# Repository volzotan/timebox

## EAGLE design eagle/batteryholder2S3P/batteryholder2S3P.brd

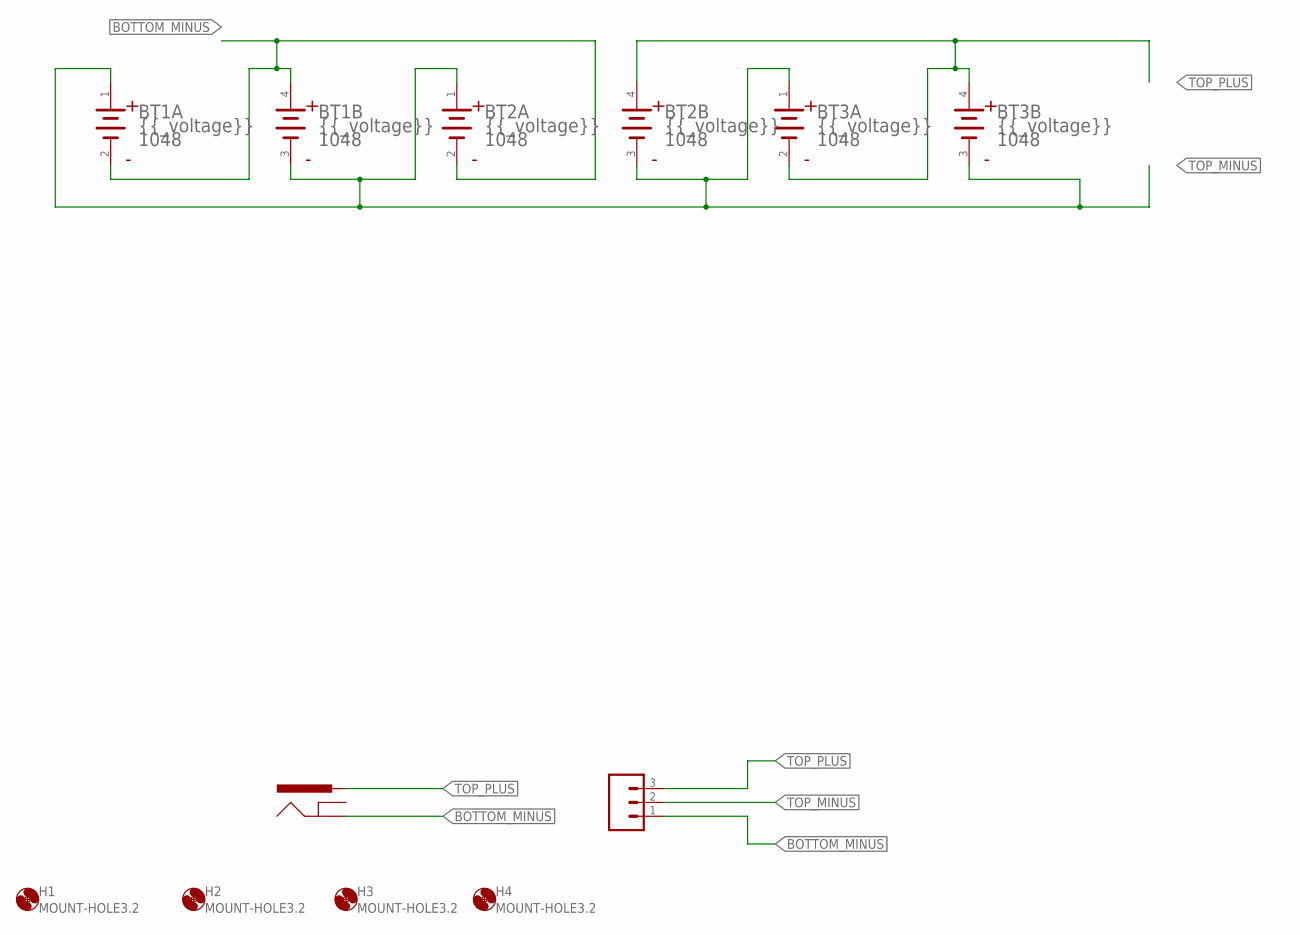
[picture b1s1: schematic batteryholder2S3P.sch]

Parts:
BT1, BT2, BT3: KEYSTONE_1048KEYSTONE_1048_0_0; KEYSTONE_1048_0
H1, H2, H3, H4: MOUNT-HOLE3.2; 3,2
J1: CONN_03-SCREW-5MM; SCREWTERMINAL-5MM-3
J3: 5.5x2.1mm Barrel; POWER_JACK_SMD

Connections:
BOTTOM_MINUS: BT1.2 (1_CATHODE), BT1.4 (2_ANODE), BT2.2 (1_CATHODE), J1.1, J3.P$4 (GND)
TOP_MINUS: BT1.1 (1_ANODE), BT1.3 (2_CATHODE), BT2.1 (1_ANODE), BT2.3 (2_CATHODE), BT3.1 (1_ANODE), BT3.3 (2_CATHODE), J1.2
TOP_PLUS: BT2.4 (2_ANODE), BT3.2 (1_CATHODE), BT3.4 (2_ANODE), J1.3, J3.VIN0 (PWR)

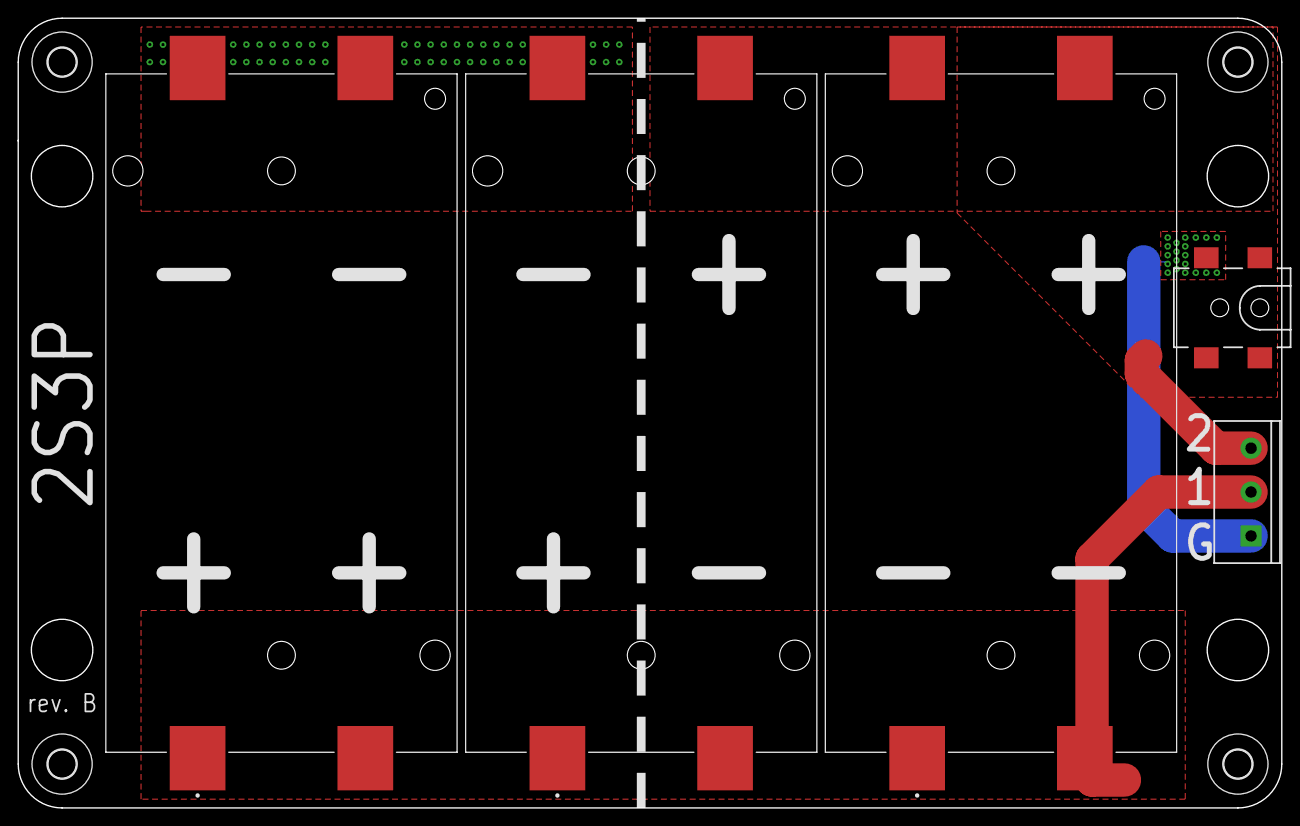
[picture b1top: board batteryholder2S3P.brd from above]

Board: 2 copper layers, 144.0 x 90.0 mm, 9 parts (0 on the bottom side), 3 nets.

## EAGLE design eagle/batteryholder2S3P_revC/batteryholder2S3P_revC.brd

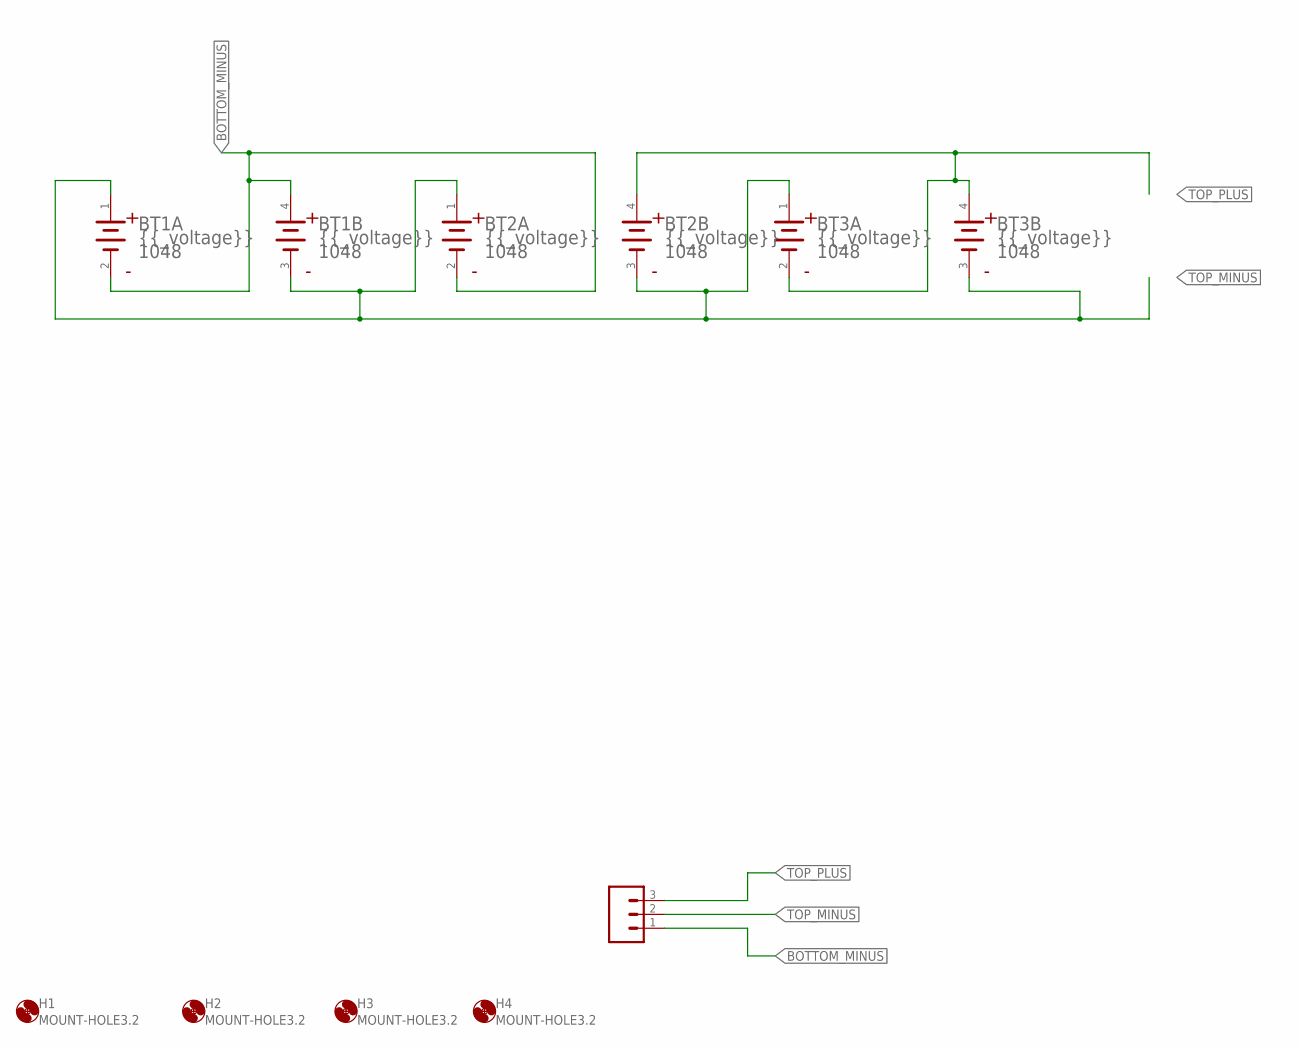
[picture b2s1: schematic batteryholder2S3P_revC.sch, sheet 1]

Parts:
BT1, BT2, BT3: KEYSTONE_1048KEYSTONE_1048_0_0; KEYSTONE_1048_0
H1, H2, H3, H4: MOUNT-HOLE3.2; 3,2
J1: CONN_03-SCREW-5MM; SCREWTERMINAL-5MM-3

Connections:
BOTTOM_MINUS: BT1.2 (1_CATHODE), BT1.4 (2_ANODE), BT2.2 (1_CATHODE), J1.1; also elsewhere on the board
TOP_MINUS: BT1.1 (1_ANODE), BT1.3 (2_CATHODE), BT2.1 (1_ANODE), BT2.3 (2_CATHODE), BT3.1 (1_ANODE), BT3.3 (2_CATHODE), J1.2; also elsewhere on the board
TOP_PLUS: BT2.4 (2_ANODE), BT3.2 (1_CATHODE), BT3.4 (2_ANODE), J1.3; also elsewhere on the board

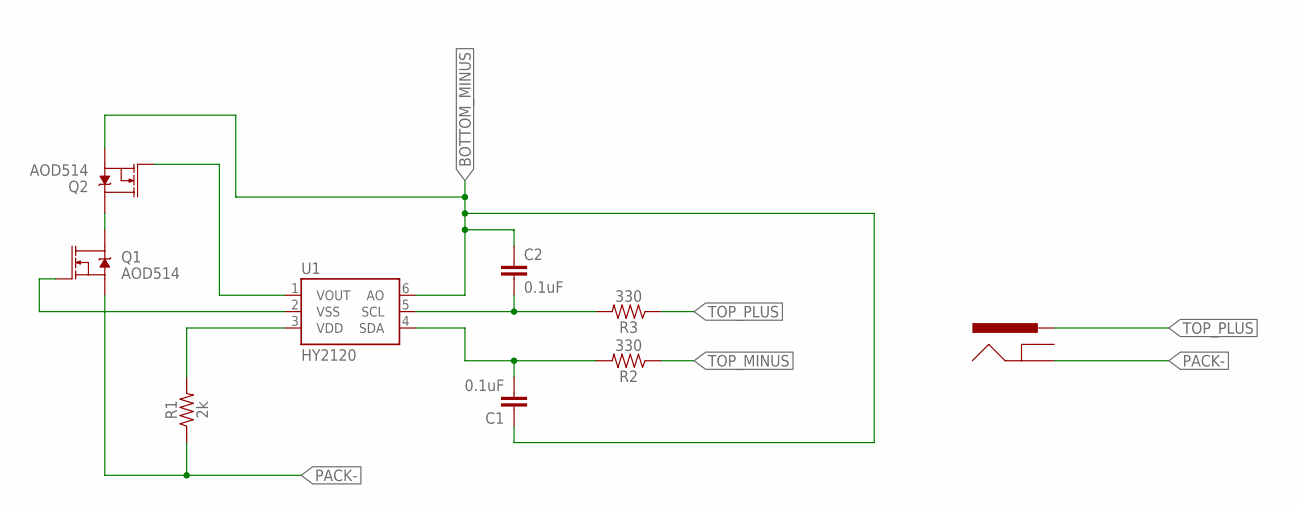
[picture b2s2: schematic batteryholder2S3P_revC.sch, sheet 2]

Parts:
C1, C2: 0.1uF; 1206
J2: POWER_JACKPTH_BREAD; POWER_JACK_PTH_BREAD
Q1, Q2: AOD514; DPAK
R1: 2k; 1206
R2, R3: 330; 1206
U1: HY2120; SOT23-6

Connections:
BOTTOM_MINUS: C1.1, C2.1, Q2.3 (S), U1.6 (AO); also elsewhere on the board
unnamed: Q2.1 (G), U1.1 (VOUT)
unnamed: Q1.1 (G), U1.2 (VSS)
unnamed: R1.2, U1.3 (VDD)
unnamed: C2.2, R3.2, U1.5 (SCL)
unnamed: C1.2, R2.2, U1.4 (SDA)
unnamed: Q1.4 (D), Q2.4 (D)
PACK-: J2.GND, Q1.3 (S), R1.1
TOP_MINUS: R2.1; also elsewhere on the board
TOP_PLUS: J2.PWR, R3.1; also elsewhere on the board

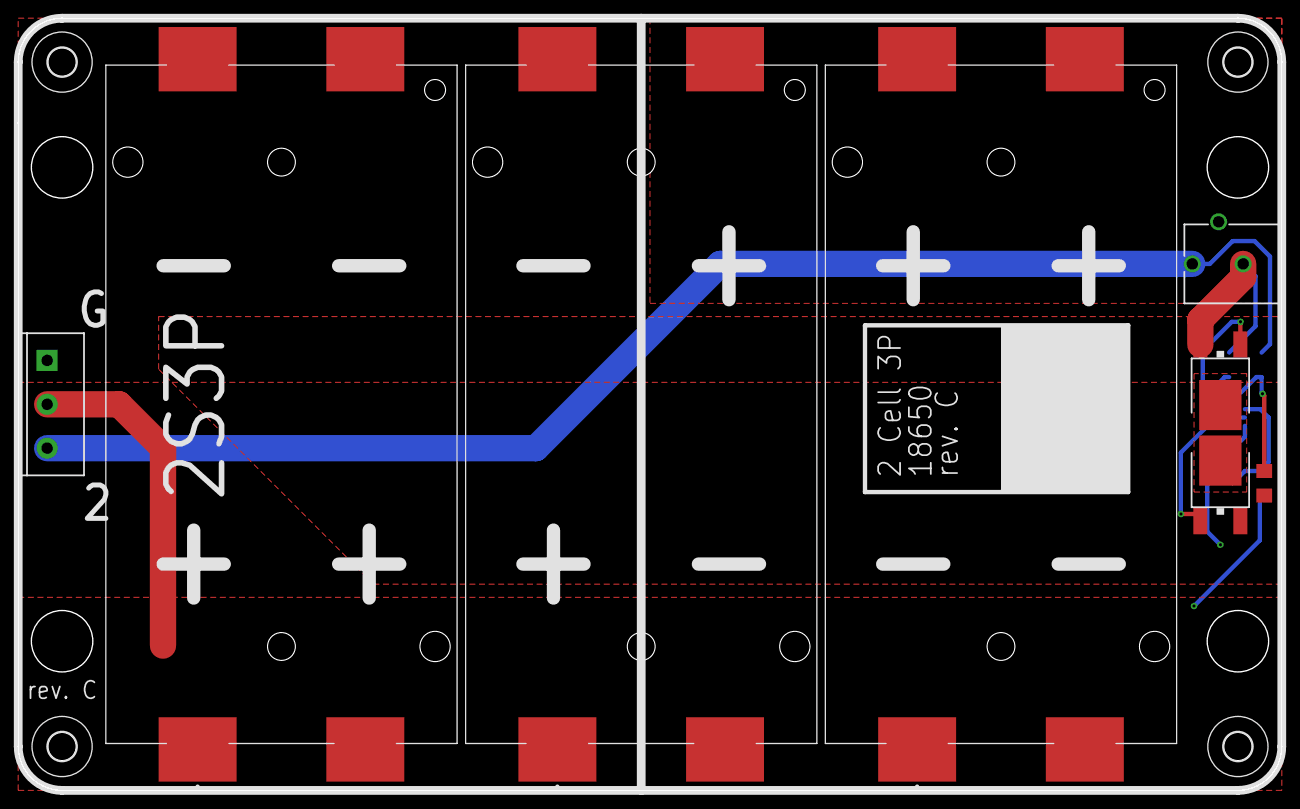
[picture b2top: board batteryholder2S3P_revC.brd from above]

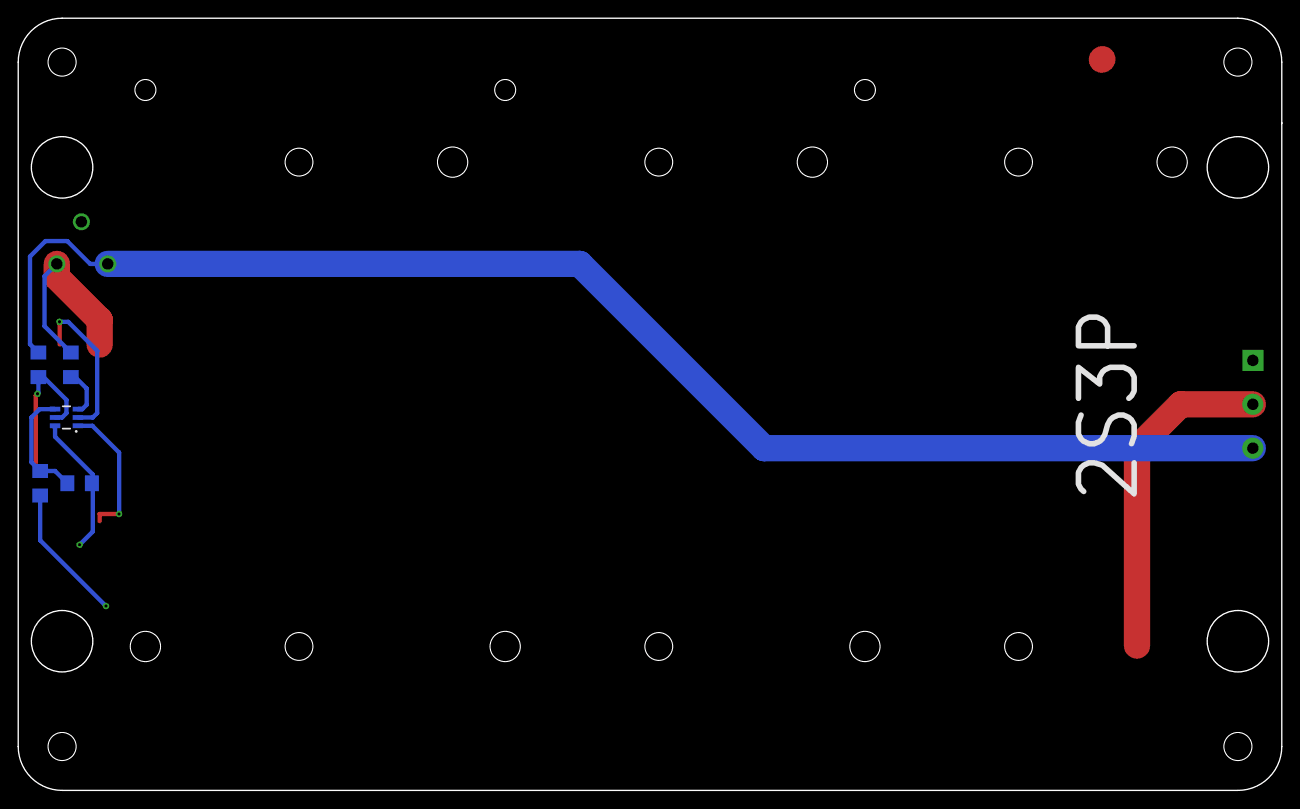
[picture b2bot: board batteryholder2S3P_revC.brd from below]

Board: 2 copper layers, 144.0 x 88.0 mm, 17 parts (5 on the bottom side), 10 nets.

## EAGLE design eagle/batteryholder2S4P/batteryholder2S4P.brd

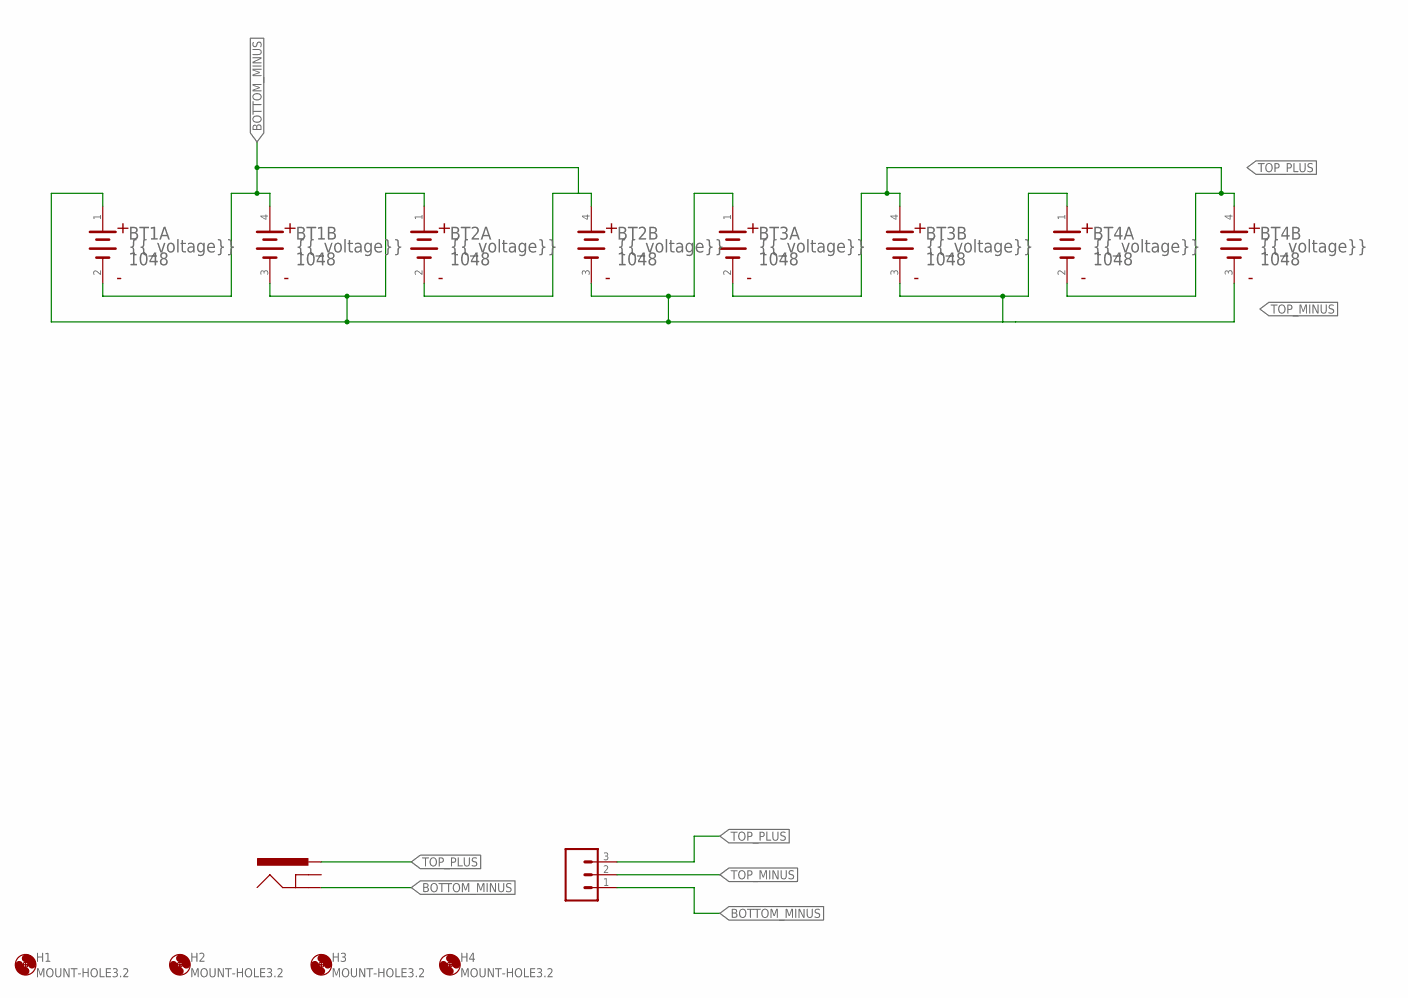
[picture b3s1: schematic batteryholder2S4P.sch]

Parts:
BT1, BT2, BT3, BT4: KEYSTONE_1048KEYSTONE_1048_0_0; KEYSTONE_1048_0
H1, H2, H3, H4: MOUNT-HOLE3.2; 3,2
J1: CONN_03-SCREW-5MM; SCREWTERMINAL-5MM-3
J3: POWER_JACKPTH_BREAD; POWER_JACK_PTH_BREAD

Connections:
BOTTOM_MINUS: BT1.2 (1_CATHODE), BT1.4 (2_ANODE), BT2.2 (1_CATHODE), BT2.4 (2_ANODE), J1.1, J3.GND
TOP_MINUS: BT1.1 (1_ANODE), BT1.3 (2_CATHODE), BT2.1 (1_ANODE), BT2.3 (2_CATHODE), BT3.1 (1_ANODE), BT3.3 (2_CATHODE), BT4.1 (1_ANODE), BT4.3 (2_CATHODE), J1.2
TOP_PLUS: BT3.2 (1_CATHODE), BT3.4 (2_ANODE), BT4.2 (1_CATHODE), BT4.4 (2_ANODE), J1.3, J3.PWR

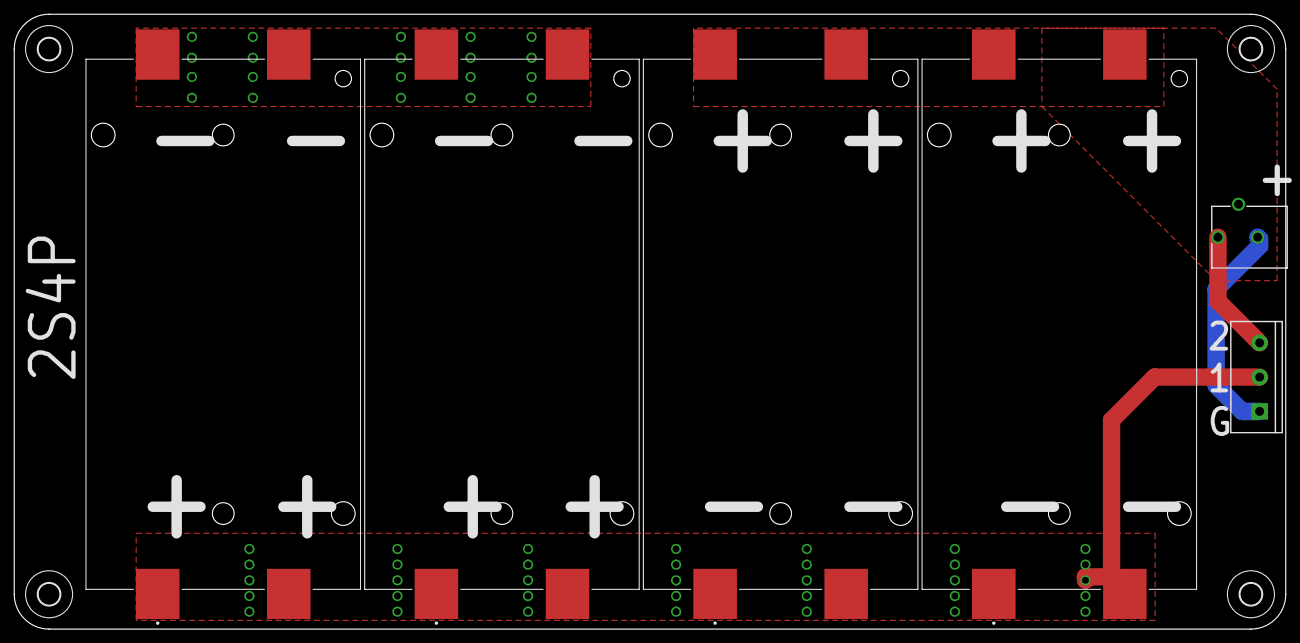
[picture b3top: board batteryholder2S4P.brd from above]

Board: 2 copper layers, 185.4 x 89.7 mm, 10 parts (0 on the bottom side), 3 nets.

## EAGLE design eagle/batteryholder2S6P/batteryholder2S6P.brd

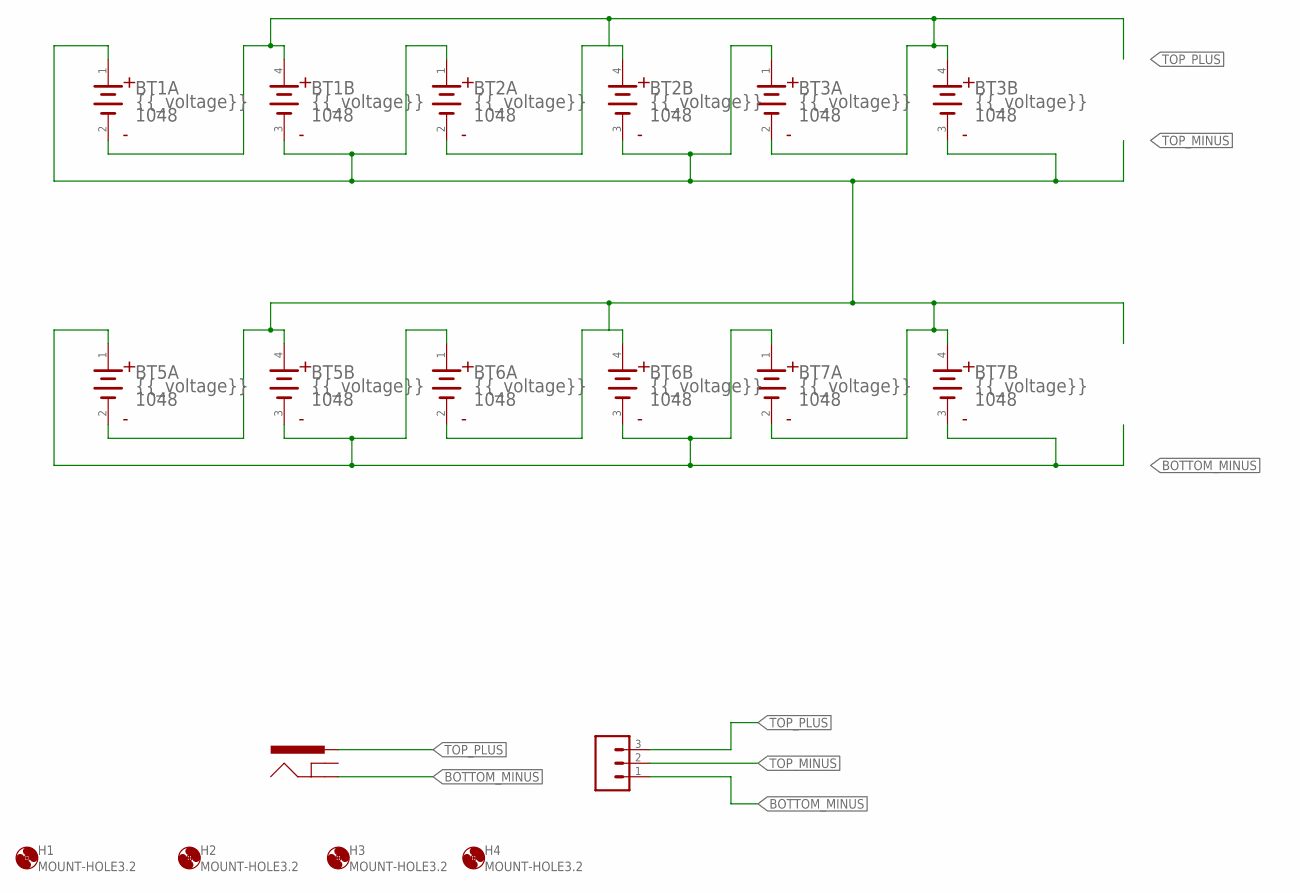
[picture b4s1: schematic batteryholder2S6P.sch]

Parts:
BT1, BT2, BT3, BT5, BT6, BT7: KEYSTONE_1048KEYSTONE_1048_0_0; KEYSTONE_1048_0
H1, H2, H3, H4: MOUNT-HOLE3.2; 3,2
J1: CONN_03-SCREW-5MM; SCREWTERMINAL-5MM-3
J3: POWER_JACKPTH_BREAD; POWER_JACK_PTH_BREAD

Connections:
BOTTOM_MINUS: BT5.1 (1_ANODE), BT5.3 (2_CATHODE), BT6.1 (1_ANODE), BT6.3 (2_CATHODE), BT7.1 (1_ANODE), BT7.3 (2_CATHODE), J1.1, J3.GND
TOP_MINUS: BT1.1 (1_ANODE), BT1.3 (2_CATHODE), BT2.1 (1_ANODE), BT2.3 (2_CATHODE), BT3.1 (1_ANODE), BT3.3 (2_CATHODE), BT5.2 (1_CATHODE), BT5.4 (2_ANODE), BT6.2 (1_CATHODE), BT6.4 (2_ANODE), BT7.2 (1_CATHODE), BT7.4 (2_ANODE), J1.2
TOP_PLUS: BT1.2 (1_CATHODE), BT1.4 (2_ANODE), BT2.2 (1_CATHODE), BT2.4 (2_ANODE), BT3.2 (1_CATHODE), BT3.4 (2_ANODE), J1.3, J3.PWR

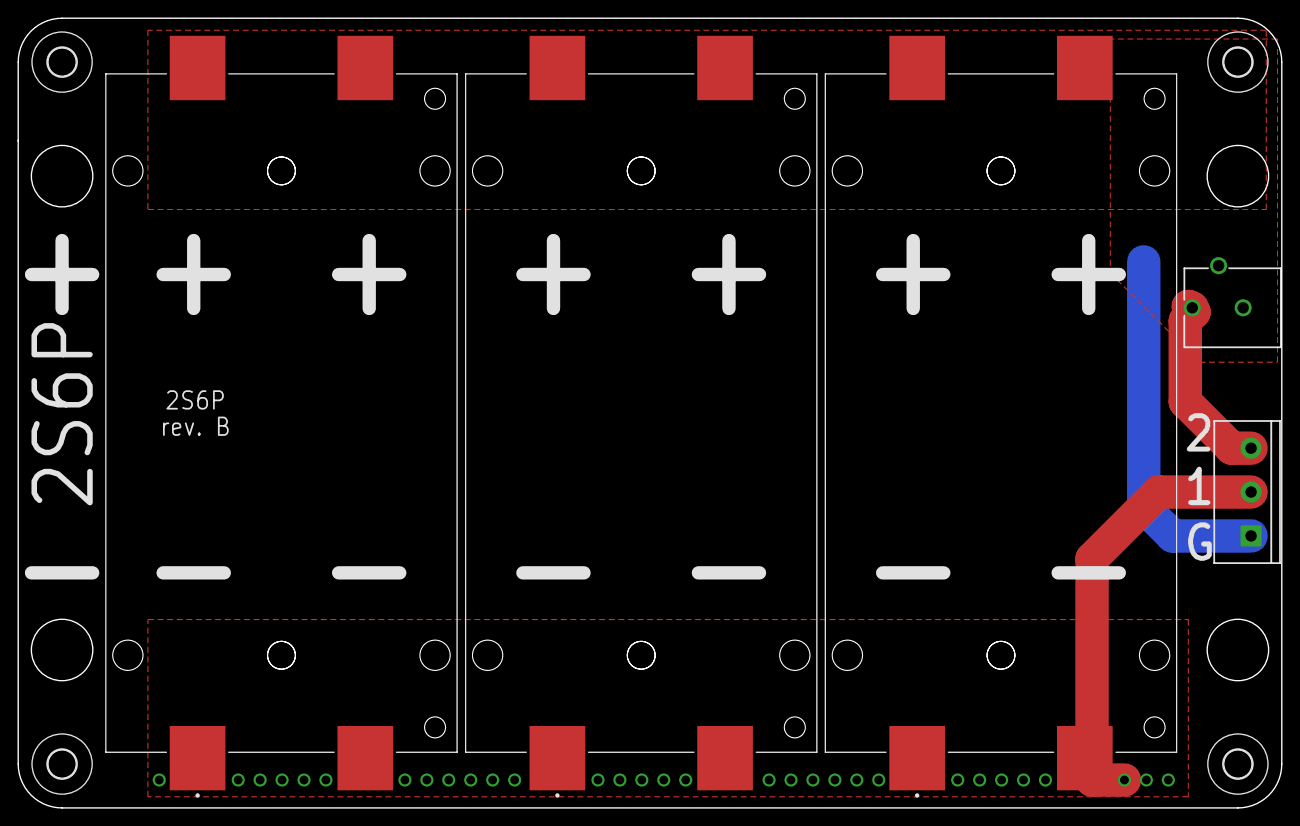
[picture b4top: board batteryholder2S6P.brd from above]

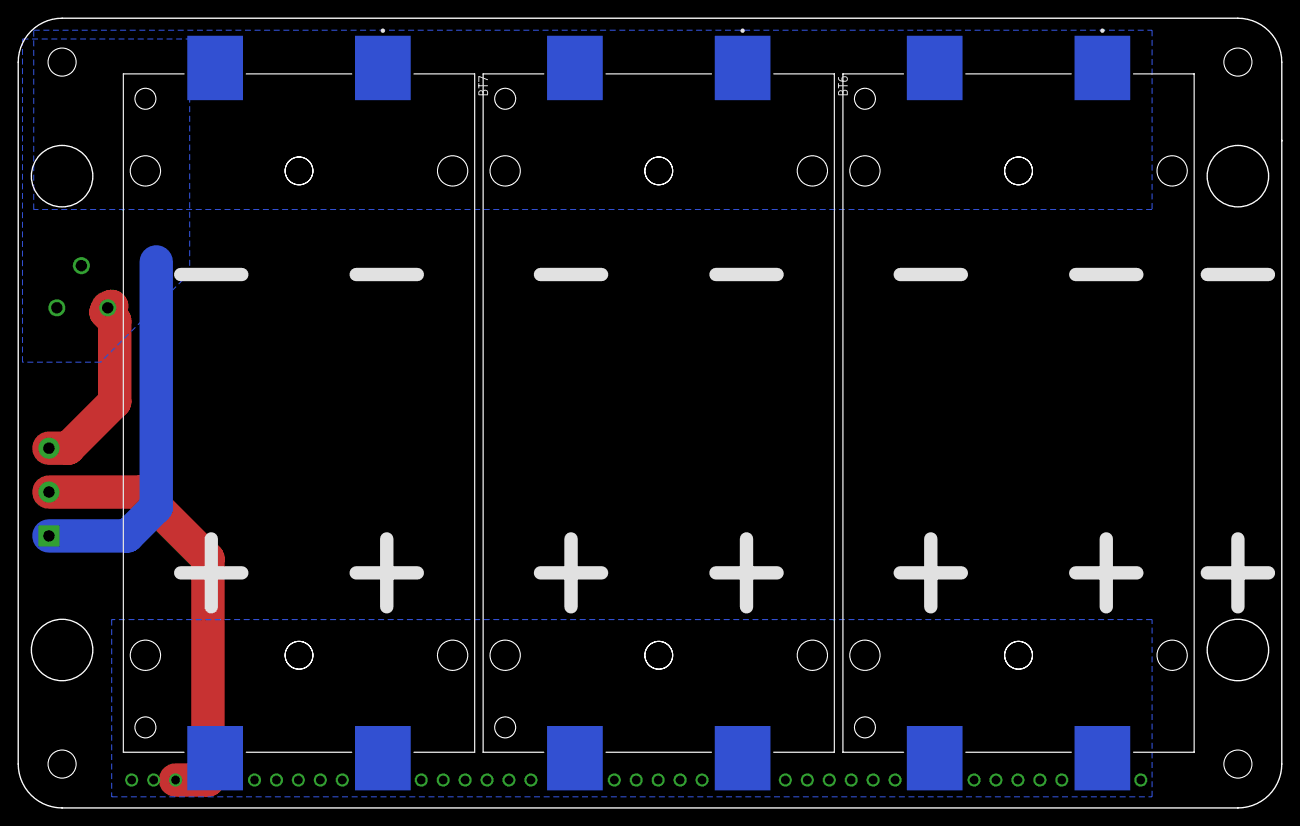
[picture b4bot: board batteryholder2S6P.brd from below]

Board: 2 copper layers, 144.0 x 90.0 mm, 12 parts (3 on the bottom side), 3 nets.

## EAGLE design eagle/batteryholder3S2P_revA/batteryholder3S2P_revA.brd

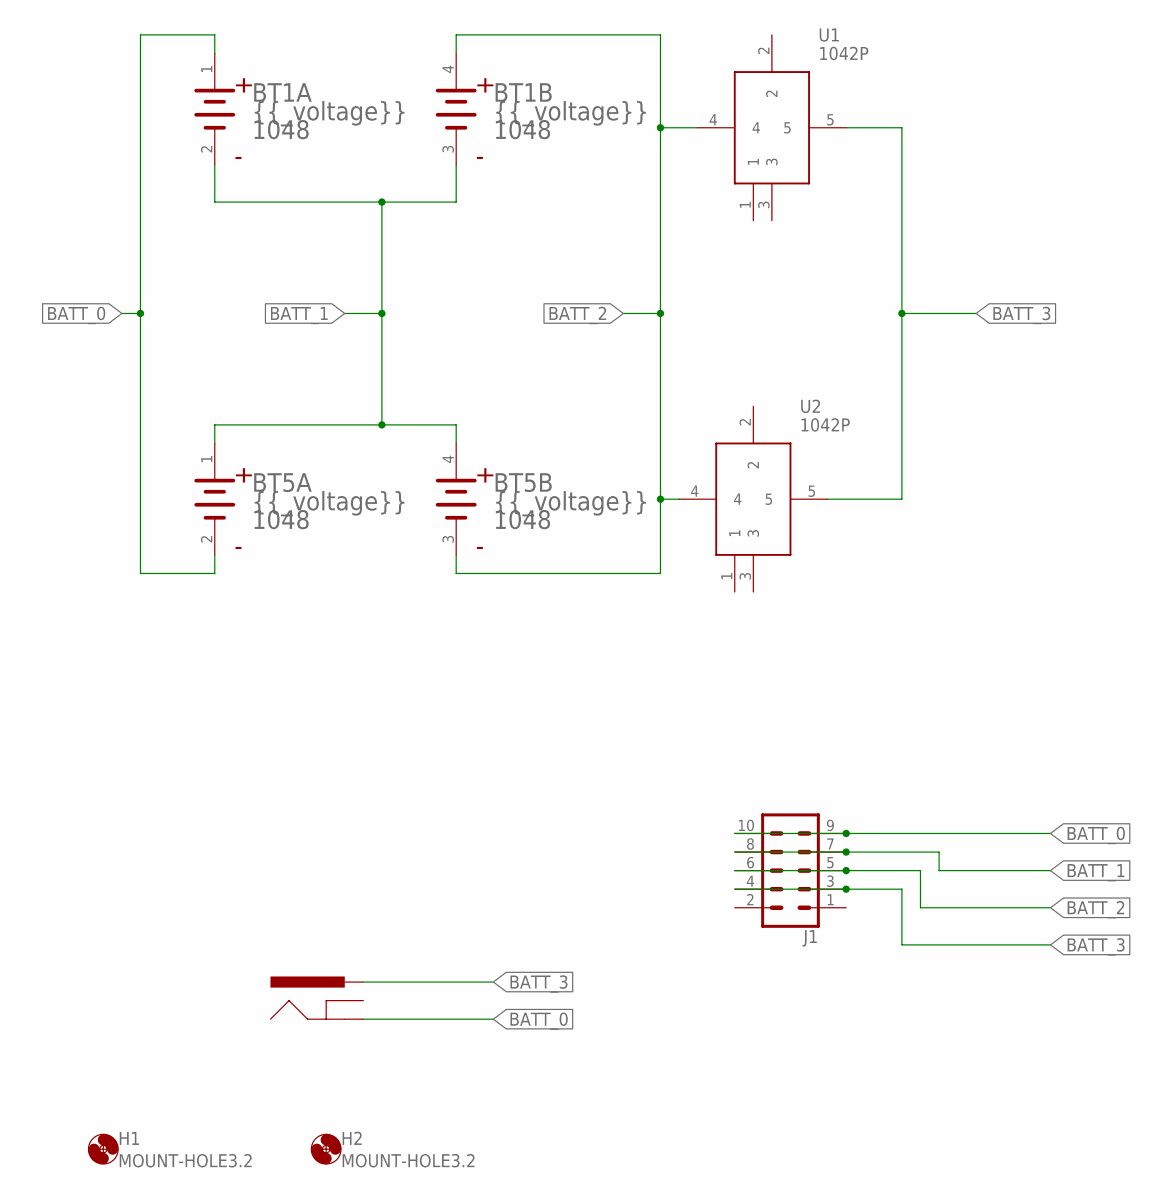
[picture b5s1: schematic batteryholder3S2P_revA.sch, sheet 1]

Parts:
BT1, BT5: KEYSTONE_1048KEYSTONE_1048_0_0; KEYSTONE_1048_0
H1, H2: MOUNT-HOLE3.2; 3,2
J1: CONN_05X2SHD; 2X5-SHROUDED
J3: POWER_JACKPTH_BREAD; POWER_JACK_PTH_BREAD
U1, U2: 1042P

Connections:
BATT_0: BT1.1 (1_ANODE), BT5.2 (1_CATHODE), J1.9, J1.10, J3.GND
BATT_1: BT1.2 (1_CATHODE), BT1.3 (2_CATHODE), BT5.1 (1_ANODE), BT5.4 (2_ANODE), J1.7, J1.8
BATT_2: BT1.4 (2_ANODE), BT5.3 (2_CATHODE), J1.5, J1.6, U1.4, U2.4
BATT_3: J1.3, J1.4, J3.PWR, U1.5, U2.5

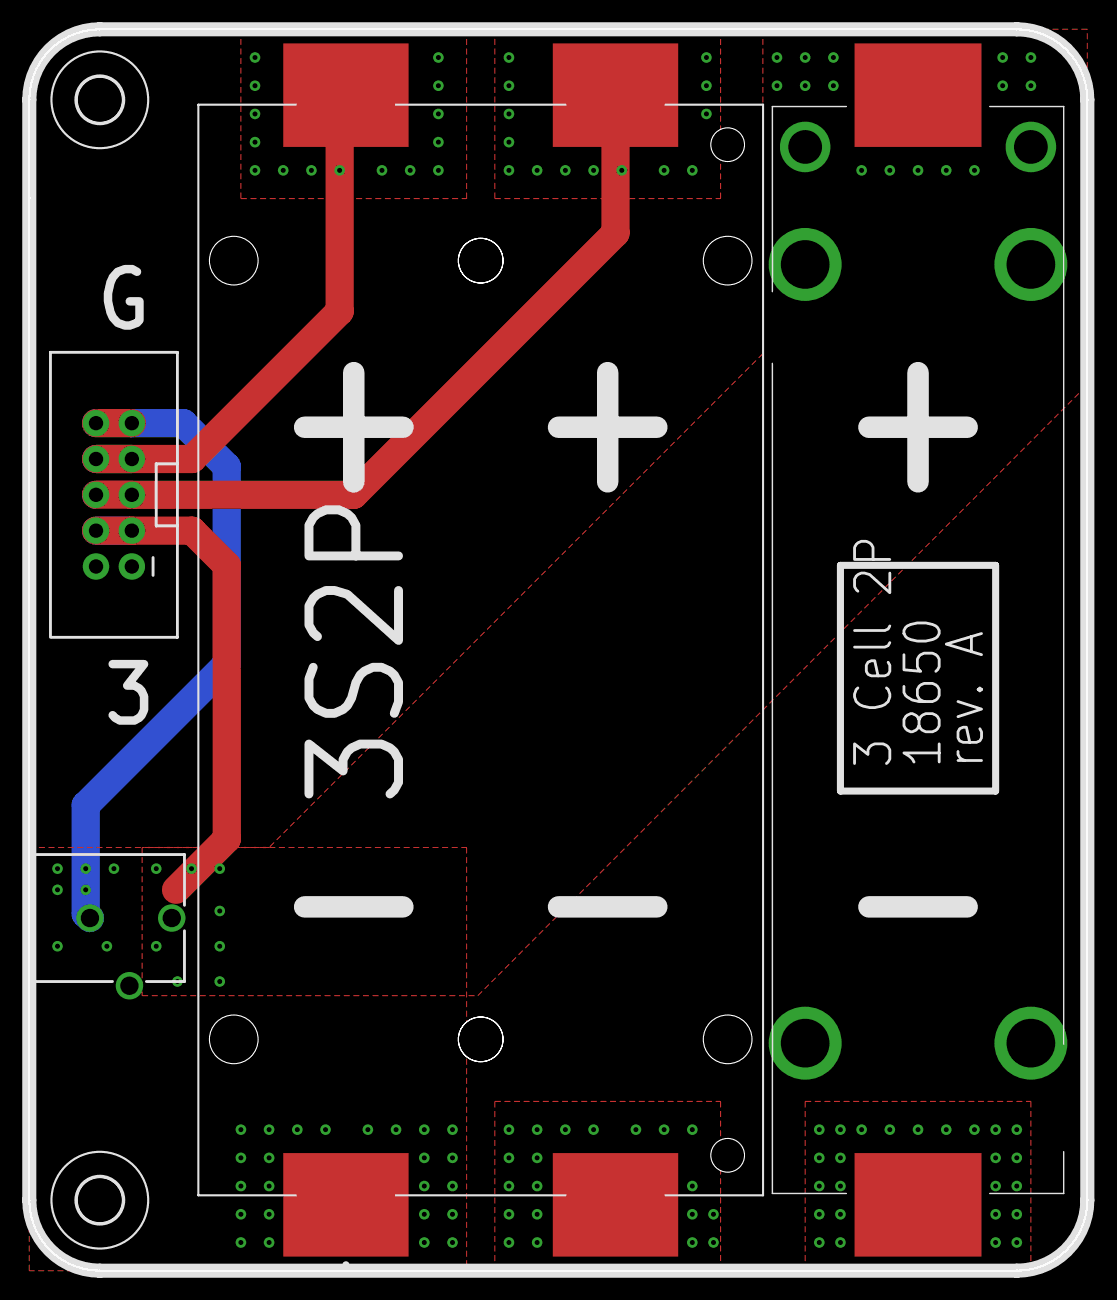
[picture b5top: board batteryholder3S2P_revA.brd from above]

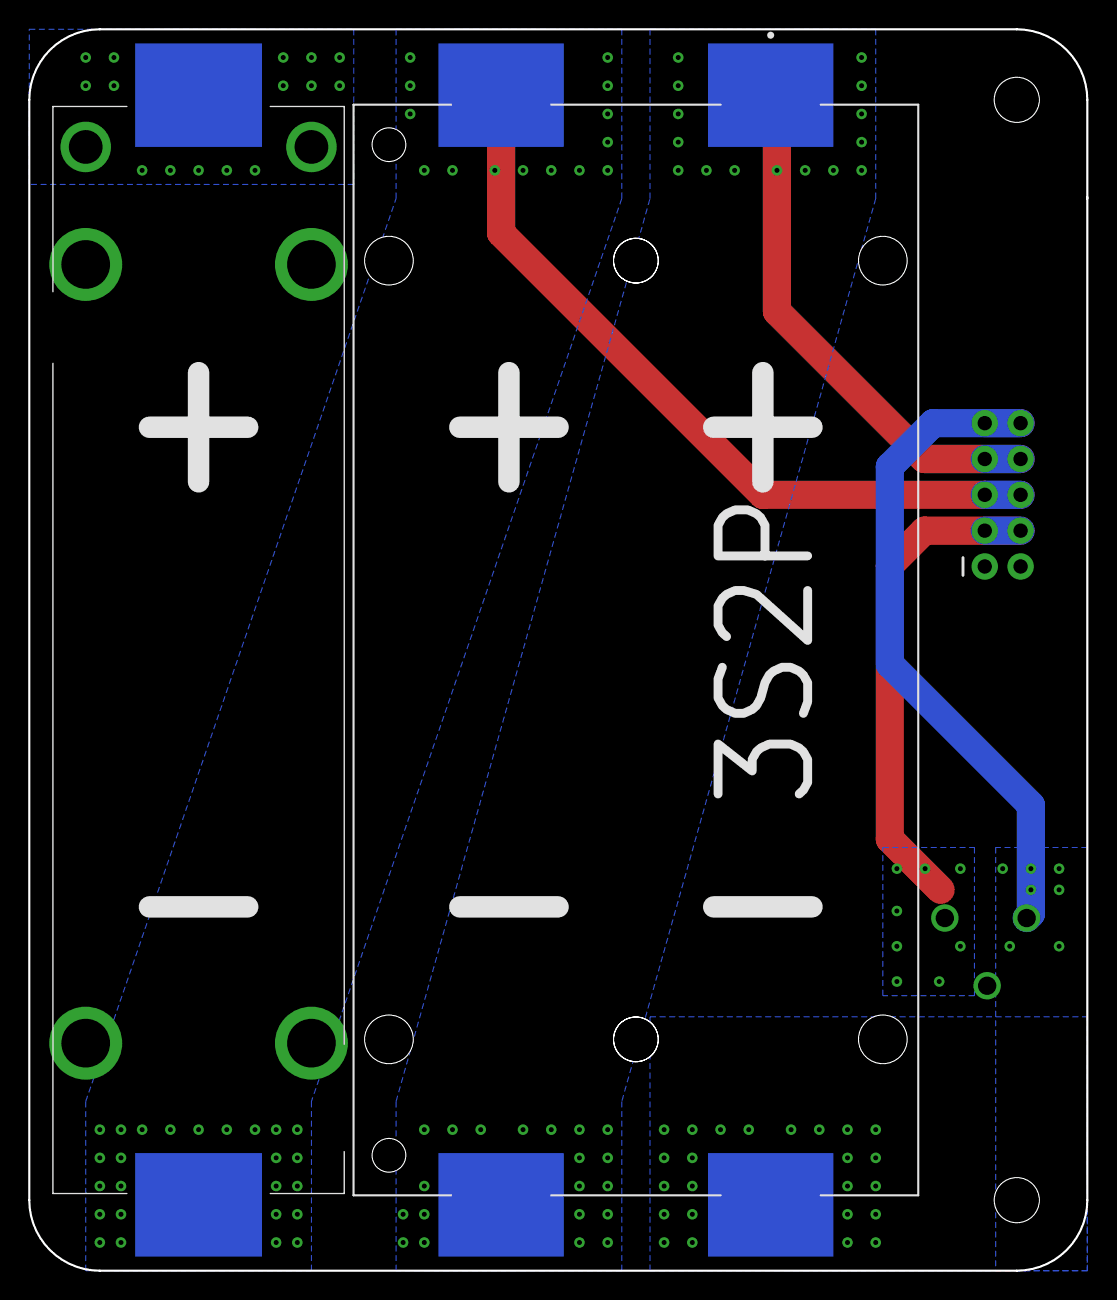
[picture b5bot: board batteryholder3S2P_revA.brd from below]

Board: 2 copper layers, 75.0 x 88.0 mm, 8 parts (2 on the bottom side), 4 nets.

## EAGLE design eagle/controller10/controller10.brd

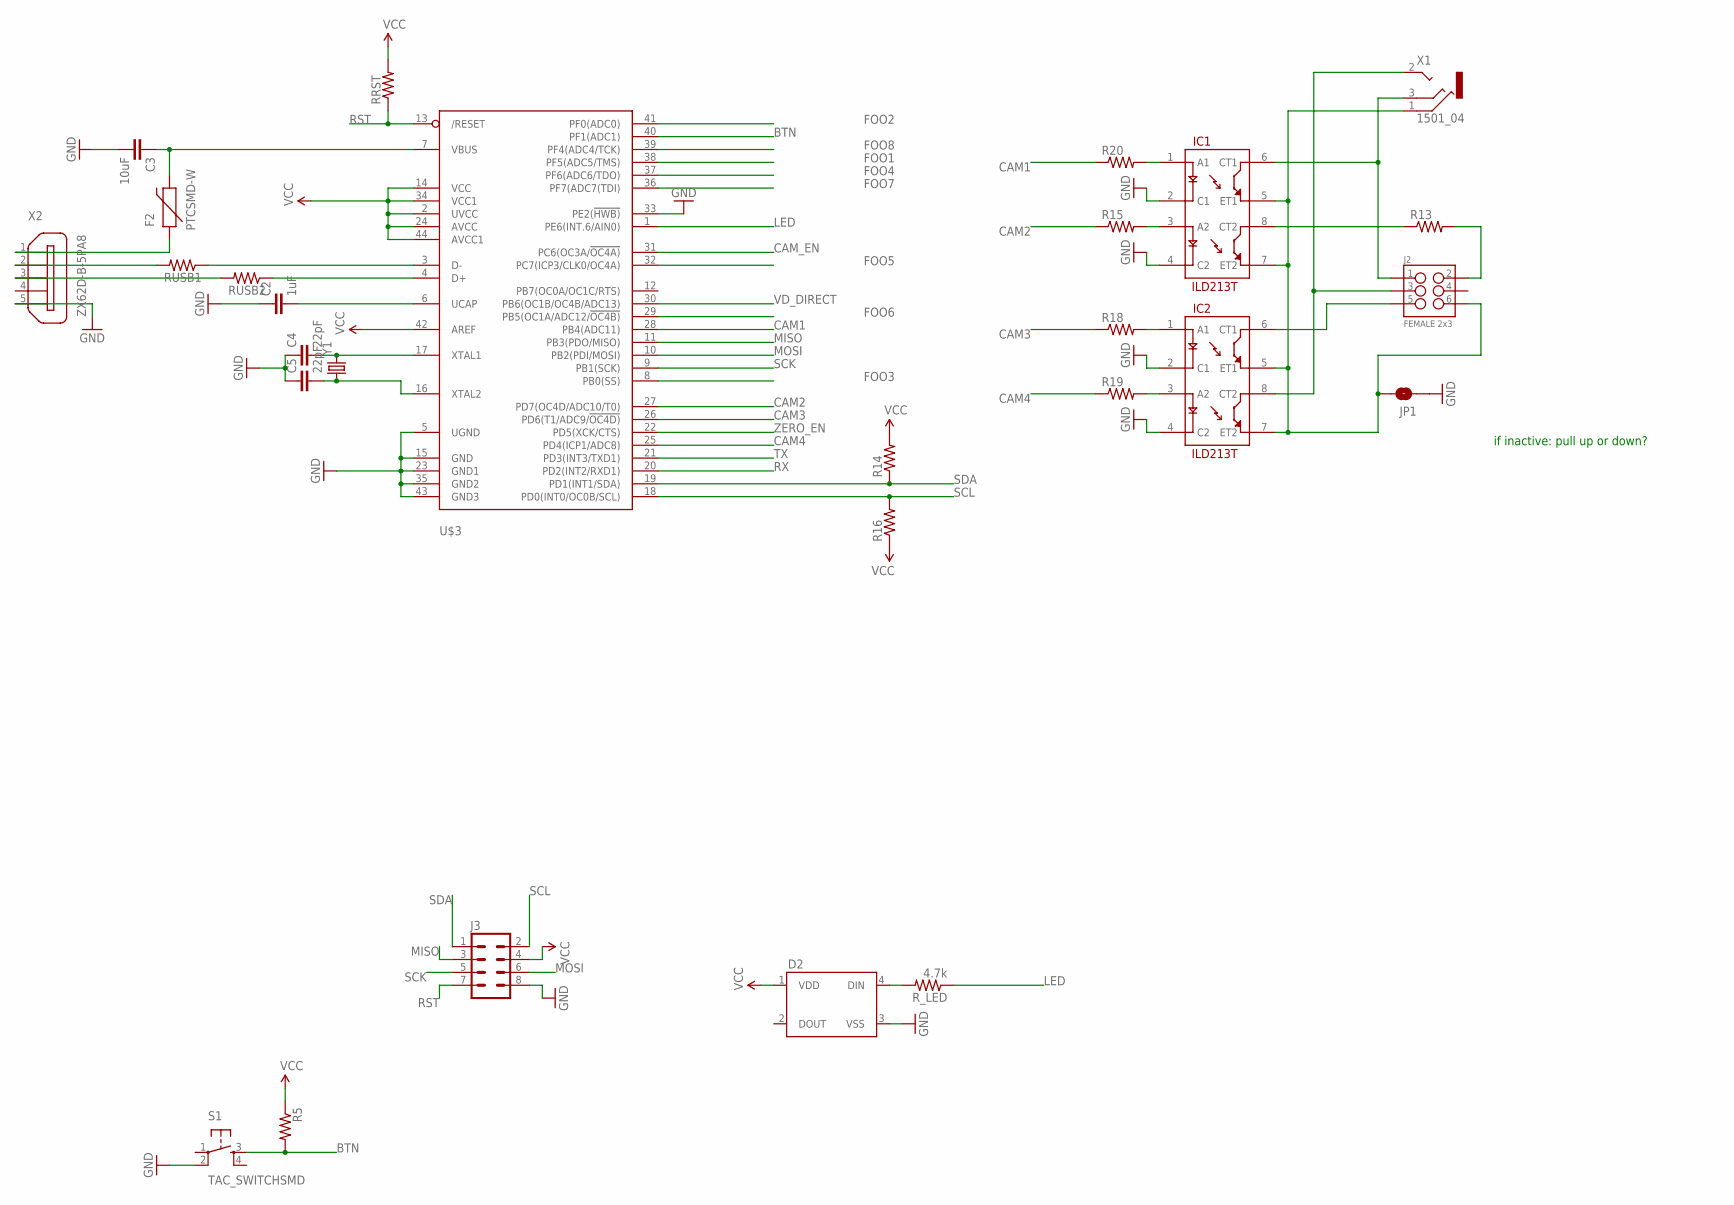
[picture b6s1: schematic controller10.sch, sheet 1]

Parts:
C2: 1uF; 1206
C3: 10uF; 1206
C4, C5: 22pF; 0805
D2: WS2812B
F2: PTCSMD-W; PTC-1206-WIDE
IC1, IC2: ILD213T; SO08
J2: FEMALE 2x3; 2X3
J3: M04X2; 2X4
JP1: JUMPER-PAD-2-NOYES_SILK; PAD-JUMPER-2-NO_YES_SILK
R5: RESISTOR1206; 1206
R13, R14, R15, R16, R18, R19, R20: RESISTOR0805-RES; 0805
RRST: RESISTOR1206; 1206
RUSB1, RUSB2: RESISTOR1206; 1206
R_LED: 4.7k; 1206
S1: TAC_SWITCHSMD; TACTILE-PTH
U$3: ATMEGA32U4-AU; TQFP44
X1: 1501_04; 1501_05
X2: ZX62D-B-5PA8
Y1: CRYSTALCRYSTAL-SMD-5X3-16MHZ; CRYSTAL-SMD-5X3

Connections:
BTN: R5.2, S1.3, U$3.40 (PF1(ADC1))
CAM1: R20.1, U$3.28 (PB4(ADC11))
CAM2: R15.1, U$3.27 (PD7(OC4D/ADC10/T0))
CAM3: R18.1, U$3.26 (PD6(T1/ADC9/!OC4D))
CAM4: R19.1, U$3.25 (PD4(ICP1/ADC8))
CAM_EN: U$3.31 (PC6(OC3A/!OC4A)); also elsewhere on the board
FOO1: U$3.38 (PF5(ADC5/TMS))
FOO2: U$3.41 (PF0(ADC0))
FOO3: U$3.8 (PB0(SS))
FOO4: U$3.37 (PF6(ADC6/TDO))
FOO5: U$3.32 (PC7(ICP3/CLK0/OC4A))
FOO6: U$3.29 (PB5(OC1A/ADC12/!OC4B))
FOO7: U$3.36 (PF7(ADC7(TDI))
FOO8: U$3.39 (PF4(ADC4/TCK))
GND: C2.1, C3.2, C4.1, C5.1, D2.3 (VSS), IC1.2 (C1), IC1.4 (C2), IC2.2 (C1), IC2.4 (C2), J3.8, JP1.1, S1.2, U$3.5 (UGND), U$3.15 (GND), U$3.23 (GND1), U$3.33 (PE2(!HWB)), U$3.35 (GND2), U$3.43 (GND3), X2.5; also elsewhere on the board
LED: R_LED.1, U$3.1 (PE6(INT.6/AIN0))
MISO: J3.3, U$3.11 (PB3(PDO/MISO))
MOSI: J3.6, U$3.10 (PB2(PDI/MOSI))
unnamed: RUSB1.1, U$3.3 (D-)
unnamed: RUSB2.1, U$3.4 (D+)
unnamed: D2.4 (DIN), R_LED.2
unnamed: C4.2, U$3.17 (XTAL1), Y1.3 (2)
unnamed: C5.2, U$3.16 (XTAL2), Y1.1
unnamed: RUSB1.2, X2.2
unnamed: RUSB2.2, X2.3
unnamed: IC2.1 (A1), R18.2
unnamed: IC2.3 (A2), R19.2
unnamed: IC1.3 (A2), R15.2
unnamed: J2.2, R13.2
unnamed: IC1.8 (CT2), R13.1
unnamed: IC1.1 (A1), R20.2
unnamed: C2.2, U$3.6 (UCAP)
unnamed: C3.1, F2.2, U$3.7 (VBUS)
unnamed: IC1.6 (CT1), J2.1, X1.3
unnamed: IC2.8 (CT2), J2.3, X1.2
unnamed: IC2.6 (CT1), J2.5
unnamed: IC1.5 (ET1), IC1.7 (ET2), IC2.5 (ET1), IC2.7 (ET2), J2.6, JP1.2, X1.1
unnamed: F2.1, X2.1
RST: J3.7, RRST.1, U$3.13 (/RESET)
RX: U$3.20 (PD2(INT2/RXD1)); also elsewhere on the board
SCK: J3.5, U$3.9 (PB1(SCK))
SCL: J3.2, R16.2, U$3.18 (PD0(INT0/OC0B/SCL))
SDA: J3.1, R14.1, U$3.19 (PD1(INT1/SDA))
TX: U$3.21 (PD3(INT3/TXD1)); also elsewhere on the board
VCC: D2.1 (VDD), J3.4, R5.1, R14.2, R16.1, RRST.2, U$3.2 (UVCC), U$3.14 (VCC), U$3.24 (AVCC), U$3.34 (VCC1), U$3.42 (AREF), U$3.44 (AVCC1); also elsewhere on the board
VD_DIRECT: U$3.30 (PB6(OC1B/OC4B/ADC13)); also elsewhere on the board
ZERO_EN: U$3.22 (PD5(XCK/CTS)); also elsewhere on the board

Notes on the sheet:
if inactive: pull up or down?

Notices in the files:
parts and their libraries:
SparkFun-Connectors: Licensing: Creative Commons ShareAlike 4.0 International - https://creativecommons.org/licenses/by-sa/4.0
